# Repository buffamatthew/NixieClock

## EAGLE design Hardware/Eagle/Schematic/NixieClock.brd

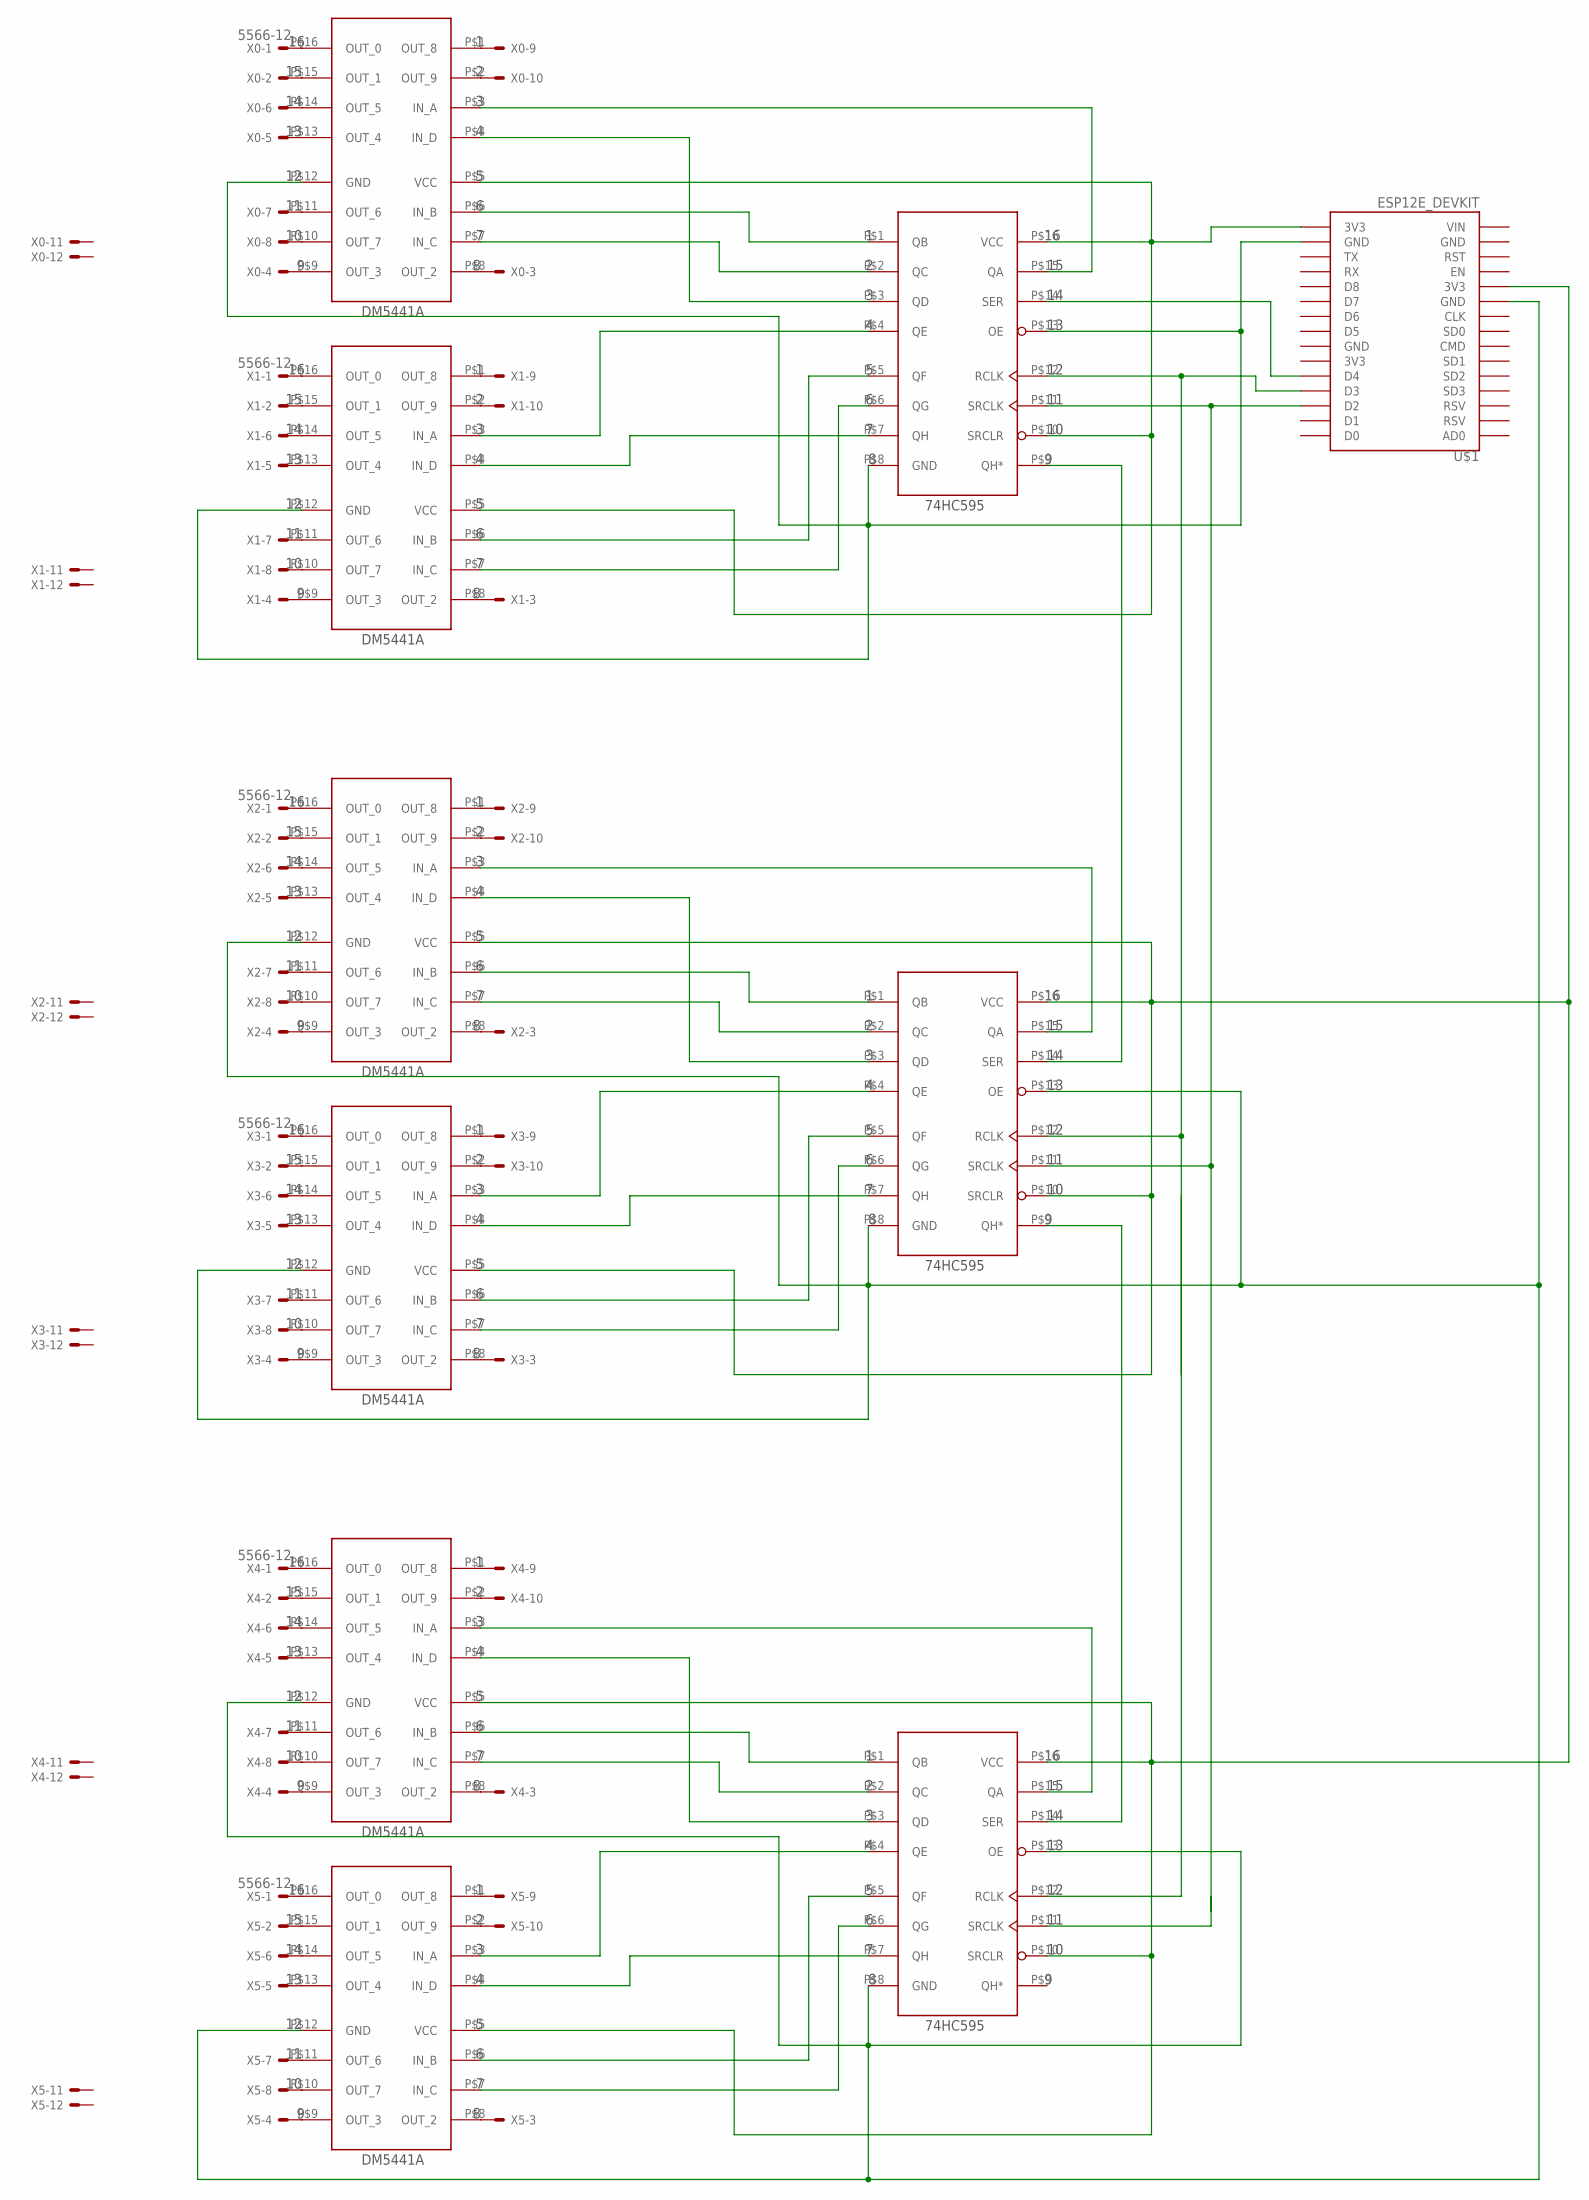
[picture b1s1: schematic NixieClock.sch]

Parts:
BCD0, BCD1, BCD2, BCD3, BCD4, BCD5: DM5441ADIP-16; DIP-16
SR0, SR1, SR2: SN74HC595NDIP-16; DIP-16
U$1: ESP12E_DEVKIT
X0, X1, X2, X3, X4, X5: 5566-12

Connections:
unnamed: BCD2.P$3 (IN_A), SR1.P$15 (QA)
unnamed: BCD0.P$3 (IN_A), SR0.P$15 (QA)
unnamed: BCD0.P$6 (IN_B), SR0.P$1 (QB)
unnamed: BCD0.P$7 (IN_C), SR0.P$2 (QC)
unnamed: BCD0.P$4 (IN_D), SR0.P$3 (QD)
unnamed: BCD1.P$3 (IN_A), SR0.P$4 (QE)
unnamed: BCD1.P$6 (IN_B), SR0.P$5 (QF)
unnamed: BCD1.P$7 (IN_C), SR0.P$6 (QG)
unnamed: BCD1.P$4 (IN_D), SR0.P$7 (QH)
unnamed: SR0.P$14 (SER), U$1.D4
unnamed: BCD0.P$8 (OUT_2), X0.3
unnamed: BCD2.P$5 (VCC), BCD3.P$5 (VCC), BCD4.P$5 (VCC), BCD5.P$5 (VCC), SR1.P$10 (SRCLR), SR1.P$16 (VCC), SR2.P$10 (SRCLR), SR2.P$16 (VCC), U$1.3V3@0 (3V3)
unnamed: BCD0.P$11 (OUT_6), X0.7
unnamed: BCD0.P$10 (OUT_7), X0.8
unnamed: BCD0.P$9 (OUT_3), X0.4
unnamed: BCD0.P$2 (OUT_9), X0.10
unnamed: BCD0.P$1 (OUT_8), X0.9
unnamed: BCD0.P$16 (OUT_0), X0.1
unnamed: BCD0.P$15 (OUT_1), X0.2
unnamed: BCD0.P$14 (OUT_5), X0.6
unnamed: BCD0.P$13 (OUT_4), X0.5
unnamed: BCD2.P$12 (GND), BCD3.P$12 (GND), BCD4.P$12 (GND), BCD5.P$12 (GND), SR1.P$8 (GND), SR1.P$13 (OE), SR2.P$8 (GND), SR2.P$13 (OE), U$1.GND@0 (GND)
unnamed: BCD2.P$6 (IN_B), SR1.P$1 (QB)
unnamed: BCD2.P$7 (IN_C), SR1.P$2 (QC)
unnamed: SR0.P$9 (QH*), SR1.P$14 (SER)
unnamed: BCD2.P$4 (IN_D), SR1.P$3 (QD)
unnamed: BCD3.P$3 (IN_A), SR1.P$4 (QE)
unnamed: BCD1.P$8 (OUT_2), X1.3
unnamed: BCD1.P$11 (OUT_6), X1.7
unnamed: BCD1.P$10 (OUT_7), X1.8
unnamed: BCD1.P$9 (OUT_3), X1.4
unnamed: BCD1.P$2 (OUT_9), X1.10
unnamed: BCD1.P$1 (OUT_8), X1.9
unnamed: BCD1.P$16 (OUT_0), X1.1
unnamed: BCD1.P$15 (OUT_1), X1.2
unnamed: BCD1.P$14 (OUT_5), X1.6
unnamed: BCD1.P$13 (OUT_4), X1.5
unnamed: BCD3.P$6 (IN_B), SR1.P$5 (QF)
unnamed: BCD3.P$7 (IN_C), SR1.P$6 (QG)
unnamed: BCD3.P$4 (IN_D), SR1.P$7 (QH)
unnamed: SR0.P$11 (SRCLK), SR1.P$11 (SRCLK), SR2.P$11 (SRCLK), U$1.D2
unnamed: BCD0.P$5 (VCC), BCD1.P$5 (VCC), SR0.P$10 (SRCLR), SR0.P$16 (VCC), U$1.3V3@2 (3V3)
unnamed: BCD0.P$12 (GND), BCD1.P$12 (GND), SR0.P$8 (GND), SR0.P$13 (OE), U$1.GND@3 (GND)
unnamed: SR1.P$9 (QH*), SR2.P$14 (SER)
unnamed: BCD2.P$8 (OUT_2), X2.3
unnamed: BCD2.P$11 (OUT_6), X2.7
unnamed: BCD2.P$10 (OUT_7), X2.8
unnamed: BCD2.P$9 (OUT_3), X2.4
unnamed: BCD2.P$2 (OUT_9), X2.10
unnamed: BCD2.P$1 (OUT_8), X2.9
unnamed: BCD2.P$16 (OUT_0), X2.1
unnamed: BCD2.P$15 (OUT_1), X2.2
unnamed: BCD2.P$14 (OUT_5), X2.6
unnamed: BCD2.P$13 (OUT_4), X2.5
unnamed: BCD3.P$8 (OUT_2), X3.3
unnamed: BCD3.P$11 (OUT_6), X3.7
unnamed: BCD3.P$10 (OUT_7), X3.8
unnamed: BCD3.P$9 (OUT_3), X3.4
unnamed: BCD3.P$2 (OUT_9), X3.10
unnamed: BCD3.P$1 (OUT_8), X3.9
unnamed: BCD3.P$16 (OUT_0), X3.1
unnamed: BCD3.P$15 (OUT_1), X3.2
unnamed: BCD3.P$14 (OUT_5), X3.6
unnamed: BCD3.P$13 (OUT_4), X3.5
unnamed: BCD4.P$3 (IN_A), SR2.P$15 (QA)
unnamed: BCD4.P$6 (IN_B), SR2.P$1 (QB)
unnamed: BCD4.P$7 (IN_C), SR2.P$2 (QC)
unnamed: BCD4.P$4 (IN_D), SR2.P$3 (QD)
unnamed: BCD5.P$3 (IN_A), SR2.P$4 (QE)
unnamed: BCD5.P$6 (IN_B), SR2.P$5 (QF)
unnamed: BCD5.P$7 (IN_C), SR2.P$6 (QG)
unnamed: BCD5.P$4 (IN_D), SR2.P$7 (QH)
unnamed: SR0.P$12 (RCLK), SR1.P$12 (RCLK), SR2.P$12 (RCLK), U$1.D3
unnamed: BCD4.P$8 (OUT_2), X4.3
unnamed: BCD4.P$11 (OUT_6), X4.7
unnamed: BCD4.P$10 (OUT_7), X4.8
unnamed: BCD4.P$9 (OUT_3), X4.4
unnamed: BCD4.P$2 (OUT_9), X4.10
unnamed: BCD4.P$1 (OUT_8), X4.9
unnamed: BCD4.P$16 (OUT_0), X4.1
unnamed: BCD4.P$15 (OUT_1), X4.2
unnamed: BCD4.P$14 (OUT_5), X4.6
unnamed: BCD4.P$13 (OUT_4), X4.5
unnamed: BCD5.P$8 (OUT_2), X5.3
unnamed: BCD5.P$11 (OUT_6), X5.7
unnamed: BCD5.P$10 (OUT_7), X5.8
unnamed: BCD5.P$9 (OUT_3), X5.4
unnamed: BCD5.P$2 (OUT_9), X5.10
unnamed: BCD5.P$1 (OUT_8), X5.9
unnamed: BCD5.P$16 (OUT_0), X5.1
unnamed: BCD5.P$15 (OUT_1), X5.2
unnamed: BCD5.P$14 (OUT_5), X5.6
unnamed: BCD5.P$13 (OUT_4), X5.5

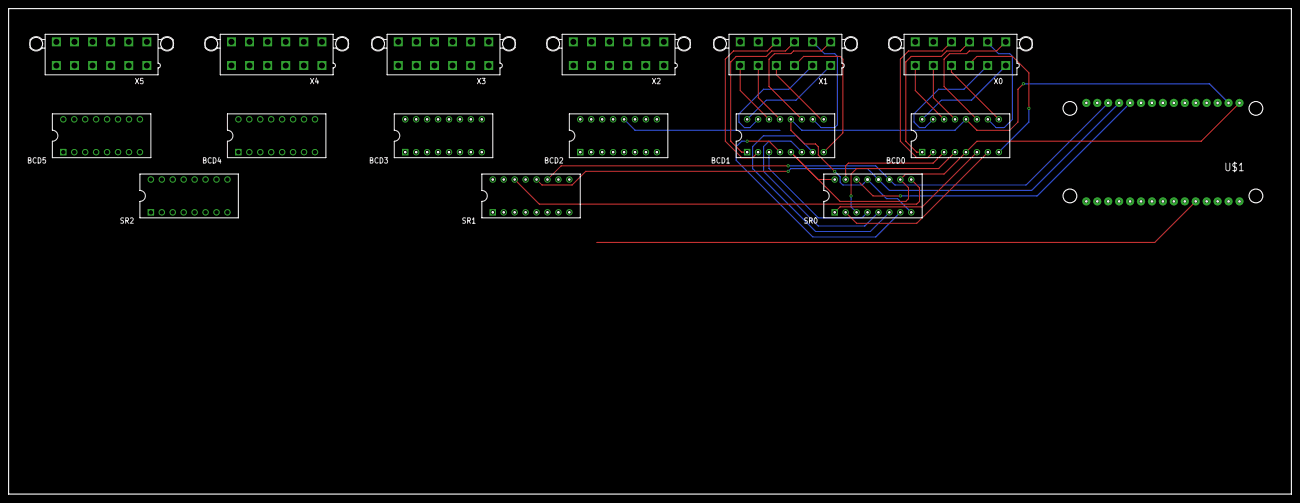
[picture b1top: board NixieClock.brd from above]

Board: 2 copper layers, 297.8 x 112.7 mm, 16 parts (0 on the bottom side), 93 nets.

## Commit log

2019-10-13 added .gitignore for DS_Store files
2019-10-13 Started making Eagle schematic. Fixed the shift register library file.
2019-10-13 Don't use last check in... missing files...
2019-10-13 Schematic progress
2019-10-13 Schematic progress.. made nixie tube driver chip lib
2019-10-13 Schematic progress... chips in board layout are out of order.. fix later
2019-10-14 Chips in board layout in correct order
2019-10-14 Shift register chips in board layout in correct order
2019-10-14 All wires from shift registers to nixie driver inputs routed
2019-10-14 Molex connectors in place.. use part 39-30-6147 on mouser
2019-10-14 Replaced 14 pin connector with 12 pin... started routing
2019-10-14 All pins routed to 1 12 pin connector.. about to start over on schematic
2019-10-14 Made schematic a lot cleaner... pins routed from 2 driver chips to 1 SR
2019-10-15 2 tubes routed
2019-10-15 Added all chips to schematic
2019-10-15 Progress
2019-10-15 Routed further chips' VCC and GND to the node's 3v3 and GND
2019-10-15 Porgress
2019-10-16 Started KiCAD Schematic
2019-10-16 KiCAD Progress
2019-10-17 Routed from one shift register to BCD.. removed gound and vcc on eagle
2019-10-17 Renamed pins on shift register in kicad
2019-10-18 Made datasheet folder.. fixed routing between SR and BCDs.
2019-10-18 Finished routing one complete stage... Now trying to make a kicad sch
2019-10-18 Progress.. about to duplicate to 3 stages
2019-10-18 All stages routed...
2019-10-19 Nixie power supply placed, HV lines routed
2019-10-19 Placed and routed buck converter
2019-10-22 Made power boards layouts, removed thick traces, reordered
    TODO:
    - Check dimmensions of power boards and node MCU
    - Add mounting holes for PCB
    - Add 3 push buttons and resistors
    - Add diode on VIN
    - Add potentiometer and ceramic resistor
2019-10-22 Made power boards layouts, removed thick traces, reordered
    TODO:
    - Check dimmensions of power boards and node MCU
    - Add mounting holes for PCB
    - Add 3 push buttons and resistors
    - Add diode on VIN
    - Add potentiometer and ceramic resistor
2019-10-22 fixed vin pin mapping
2019-10-22 Added Vin Diode
2019-10-23 Routed 3 buttons and resistors, routed dimming HW,
2019-10-26 Reading time successfully. Added drivers to communicate with NodeMCU.
2019-10-26 Routed all cathodes to RGB LEDs
2019-10-26 Routed holes for nixie tube resistors
2019-10-27 Routed RGB LED resistors
2019-10-27 started finishing routing to nixie driver chip.
2019-10-27 Finished routing all pins to BCD encoders
2019-10-28 done?
2019-10-31 Made input headers wider pitch
2019-11-03 Updated shift register pins to match PCB.. progress on newNixieDrv
2019-11-04 Nixie function working
2019-11-04 Cleaned up newDrvNixie files
2020-02-24 Added test mode... not tested yet.
